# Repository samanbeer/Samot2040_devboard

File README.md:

# SamotPi2040 DevBoard

---

## 📌 Project Overview & Purpose

- **What is it?** A standalone development board based on the Raspberry Pi RP2040 dual-core ARM Cortex-M0+ processor.
- **What does it do?** It provides all essential supporting circuitry (power regulation, Li-Po 3.7V battery charging, automatic power source switching, high-speed crystal oscillator, SPI flash, USB termination, and ESD/pull-down configuration) to run MicroPython, CircuitPython, Arduino, or bare-metal C/C++ Pico SDK code.
- **Why does it exist?** It was created to explore custom PCB design from scratch, master 2-layer routing with fine-pitch QFN and 0402 components, and build a reliable, inexpensive, and customizable devboard for prototyping robotics and embedded electronics.

---

## Why I Made This Project

Because I wanted to design my own RP2040 board with my own design a to be able to say "I made this" with:
1. A modern **USB-C** connector
2. Integrate both **BOOT** and **RESET** switches directly on board to make flashing easy.
3. Provide a full 8MB high-speed SPI Flash storage for large CircuitPython scripts, assets, and datalogging.
4. Integrated **Li-Po 3.7V battery charging** (MCP73831) and **automatic power source switching** (BAT54C Schottky diode) for portable projects.

---

## Project Gallery

### 3D Render

### 3D Board View

### PCB Layout & Routing

### Schematic

---

## Hardware Features & Specifications

| Feature | Specification |
| --- | --- |
| **Microcontroller** | Raspberry Pi RP2040 (Dual-core ARM Cortex-M0+ up to 133 MHz, 264 KB on-chip SRAM) |
| **Flash Memory** | 8 MB (64 Mbit) SPI Flash (Macronix MX25L6433FM2I-08G, SOIC-8) |
| **Power Input** | USB-C 5V VBUS or Li-Po / Li-Ion 3.7V Battery |
| **Battery Charger** | Microchip MCP73831-2-OT (Single-cell Li-Po/Li-Ion linear charge manager, 4.2V CC/CV) |
| **Power Multiplexing** | BAT54C dual Schottky barrier diode (automatic power source switching between USB and Battery) |
| **Voltage Regulation** | Microchip MCP1700T-3302E/TT (3.3V Low-Dropout Regulator, **250mA** output) |
| **Expansion / I/O** | 2x 1x20-pin 2.54mm pitch headers (breadboard compatible) |

---

##  Power Management & Battery Support

The board features a built-in power management circuit designed for both desktop development and portable battery-powered operation:

- **3.7V Li-Po / Li-Ion Battery Support:** Connect any standard 3.7V single-cell Lithium-Polymer (Li-Po) or Lithium-Ion (Li-Ion) battery to the `+BATT` and `GND` pins/pads.
- **Integrated Battery Charging:** The on-board **Microchip MCP73831** charge controller automatically charges the battery when connected to USB-C (5V VBUS) using constant current / constant voltage (CC/CV) up to 4.2V.
- **Automatic Power Source Switching:** A dual common-cathode Schottky diode (**BAT54C**) acts as an automatic power OR-ing switch. When USB-C is plugged in, the board runs directly from USB power while recharging the battery. When USB-C is disconnected, power seamlessly falls over to the battery without interruption or board resets.

---

## 🛠️ Step-by-Step Assembly Guide

> [!IMPORTANT]
> I recommend using HOT airflow station or hot plate for soldering because there are really small components like the main chip or 0402 capacitors/resistors

### Required Tools
- Hot air station / hot plate and soldering iron
- solder flux paste / pen and solder wick
- tweezers
- USB-C data cable

### Assembly Steps

1. **Solder the RP2040 chip:**
   - Apply a thin layer of solder paste to the center thermal pad and other pads.
   - Align first pin of the RP2040 chip using the silkscreen dot marker.
   - Reflow using hot air (~320°C–350°C) or hot plate. Make sure the chip is centered.
2. **Solder the Flash (U3), Voltage Regulator (U2), Charger (U4), and Diode (D1):**
   - Solder the MX25L6433 flash chip (SOIC-8), MCP1700 (SOT-23), MCP73831 charger (SOT-23-5), and BAT54C diode (SOT-23). You can do this with normal soldering iron and plenty of flux.
3. **Solder Passives (Resistors & Capacitors) and Crystal:**
   - Solder the small 0402 capacitors (C1–C12, C17, C18) close to the RP2040 power pins.
   - Solder the 0603 capacitors (C13, C14), crystal load capacitors (C15, C16), and resistors (R1–R7, R9).
   - Then carefully solder the 12 MHz crystal (Y1).
4. **Solder USB-C (J1):**
   - Align the 16-pin USB-C receptacle (GCT USB4085). Solder the through-hole shielding legs for mechanical strength, then use a iron tip with a lot of flux to solder the other pins.
5. **Solder buttons(SW1, SW2):**
   - Solder the swithces for BOOT and RESET.
6. **Double check :**
   - Inspect all solder joidnts under magnification for solder bridges or cold joints (especially on the RP2040 and USB-C).
   - Using a multimeter in continuity/resistance mode, verify that `VBUS` (5V), `3V3`, and `GND` are **not shorted**.
7. **Solder Pin Headers (J2, J3, ):**
   - Insert the 1x20 2.54mm male headers into a solderless breadboard to keep them perpendicular, place the PCB on top, and solder each pin.

---

##  How to Flash Firmware

The RP2040 has a built-in ROM bootloader that makes flashing firmware simple without requiring external programmers:

```mermaid
flowchart LR
    A["Hold BOOT"] --> B["Plug in USB-C"]
    B --> C["'RPI-RP2' Drive Appears"]
    C --> D["Drag & Drop .UF2 File"]
    D --> E["Auto Reboot & Run!"]
```

1. **Enter Bootloader Mode:**
   - Hold the **`BOOT`** button (SW1).
   - Connect the board to computer using a USB-C data cable 
   - Release the `BOOT` button.
3. **Flashing Firmware:**
   - Drag and drop your compiled **`.uf2`** firmware file onto the `RPI-RP2` drive that should appear on PC:
     - **MicroPython:** Download the [Official RP2040 MicroPython UF2](https://micropython.org/download/rp2-pico/).
     - **CircuitPython:** Download the [Adafruit CircuitPython RP2040 UF2](https://circuitpython.org/board/raspberry_pi_pico/).
     - **C/C++ SDK / Arduino:** Build your project using Arduino IDE (with Earle Philhower RP2040 core) or Pico SDK and drag the resulting `.uf2` file.
4. **Execution:**
   - Once the `.uf2` file finishes copying, the board will automatically dismount and execute the program immediately.

---

## BOM

> Import [`quickOrder_TME.csv`](quickOrder_TME.csv) directly to [TME.eu](https://tme.eu) for fast order.

| Qty | Value | Reference | Footprint | Where | Cost (USD) |
|:---:|:---|:---|:---|:---|:---:|
| 1 | **RP2040** | U1 | QFN-56-1EP (7x7mm, 0.4mm pitch) | [TME LINK](https://www.tme.eu/cz/details/sc0914-7/raspberry-pi-vestavene-systemy/raspberry-pi/ic-rp2040-rp2b2-t-r-500-7-reel/) | $1.02 |
| 1 | **MX25L6433FM2I-08G** (8MB Flash) | U3 | SOIC-8 (5.3x5.3mm, 1.27mm pitch) | [TME LINK](https://www.tme.eu/cz/details/mx25l6433fm2i-08g/pameti-flash-seriove/macronix-international/mx25l6433fm2i-08g-tube/) | $2.40 |
| 1 | **MCP1700T-3302E/TT** (3.3V LDO) | U2 | SOT-23 | [TME LINK](https://www.tme.eu/cz/details/mcp1700t-3302e_tt/stabilizatory-napeti-neregulovane-ldo/microchip-technology/) | $0.65 |
| 1 | **12 MHz Crystal** | Y1 | SMD 3225-4Pin (3.2x2.5mm) | [TME LINK](https://www.tme.eu/cz/details/abm8g-12.000mhz-18/resonators-and-generators/abracon/abm8g-12-000mhz-18-d2y-t/) | $0.39 |
| 1 | **USB-C Receptacle 16P** | J1 | GCT_USB4105 | [TME LINK](https://www.tme.eu/cz/details/usb4105-gf-a/konektory-usb-a-ieee1394/gct/) | $0.75 |
| 2 | **Tactile Switch SPST** | SW1, SW2 | SMD (Omron B3U-1000P-B) | [TME LINK](https://www.tme.eu/cz/details/b3u-1000pb/mikrospinace-tact/omron-electronic-components/b3u-1000p-b/) | $1.95 |
| 12 | **0.1 µF (100nF) 16V** | C2, C3, C4, C5, C6, C7, C8, C9, C11, C12, C17, C18 | C_0402 (1005 Metric) | [TME LINK](https://www.tme.eu/cz/details/grm155r71c104ka88d/kondenzatory-mlcc-smd/murata/) | $0.17 |
| 2 | **1 µF 25V** | C1, C10 | C_0402 (1005 Metric) | [TME LINK](https://www.tme.eu/cz/details/grm155r61e105ma12d/kondenzatory-mlcc-smd/murata/) | $0.095 |
| 4 | **10 µF 10V** | C13, C14, C19, C20 | C_0603 (1608 Metric) | [TME LINK](https://www.tme.eu/cz/details/lmk107bj106maltd/kondenzatory-mlcc-smd/taiyo-yuden/lmk107-bj106maltd/) | $0.60 |
| 2 | **27 pF 50V** | C15, C16 | C_0603 (1608 Metric) | [TME LINK](https://www.tme.eu/cz/details/cc0603jrnpo9270/kondenzatory-mlcc-smd/yageo/cc0603jrnpo9bn270/) | $0.043 |
| 2 | **27 Ω 1%** | R3, R4 | R_0402 (1005 Metric) | [TME LINK](https://www.tme.eu/cz/details/erj2rkf27r0x/rezistory-smd/panasonic/) | $0.25 |
| 2 | **5.1 kΩ 1%** | R1, R2 | R_0603 (1608 Metric) | [TME LINK](https://www.tme.eu/cz/details/wr06x5101ftl/rezistory-smd/walsin/) | $0.18 |
| 2 | **1 kΩ 1%** | R5, R6 | R_0603 (1608 Metric) | [TME LINK](https://www.tme.eu/cz/details/crcw06031k00fkea/rezistory-smd/vishay/) | $0.015 |
| 2 | **10 kΩ 1%** | R7, R8, R9 | R_0603 (1608 Metric) | [TME LINK](https://www.tme.eu/cz/details/rc0603jr-0710k/rezistory-smd/yageo/rc0603jr-0710kl/) | $0.15 |
| 2 | **Pin Header 1x20 (2.54mm)** | J2, J3 | PinHeader_1x20_P2.54mm_Vertical | [TME LINK](https://www.tme.eu/cz/details/sl8.20z/konektory-hrebinky/fischer-elektronik/10057879/) | $4.5(I dont need these. Already own) |
| 1 | **MCP73831-2-OT** | U4 | SOT-23-5_HandSoldering | [TME LINK](https://www.tme.eu/cz/details/mcp73831t-2aci_ot/kontrolery-baterii-a-akumulat-obvody/microchip-technology/) | ~$0.75 |
| 1 | **BAT54C** | D1 | SOT-23_Handsoldering | [TME LINK](https://www.tme.eu/cz/details/bat54c-aks/diody-schottky-smd/akyga-semi/aks0016/) | ~$0.07 |
| 1 | **Li-Po 3.7V Battery** | - | - | [TME LINK](https://www.tme.eu/cz/details/aky-lp401235/akumulatory/akyga-battery/aky0475/) | ~$5.7 |
| 1 | **PCB ** | PCB | 2-layer FR-4 (1.6mm, ENIG/HASL) | [JLCPCB](https://jlcpcb.com) | ~$13.45 |
| - | **Estimated Shipping** | - | - | - | ~$8.21 |
| **Total** | | | | | **~$41,34** |

### JLCPCB Cart:

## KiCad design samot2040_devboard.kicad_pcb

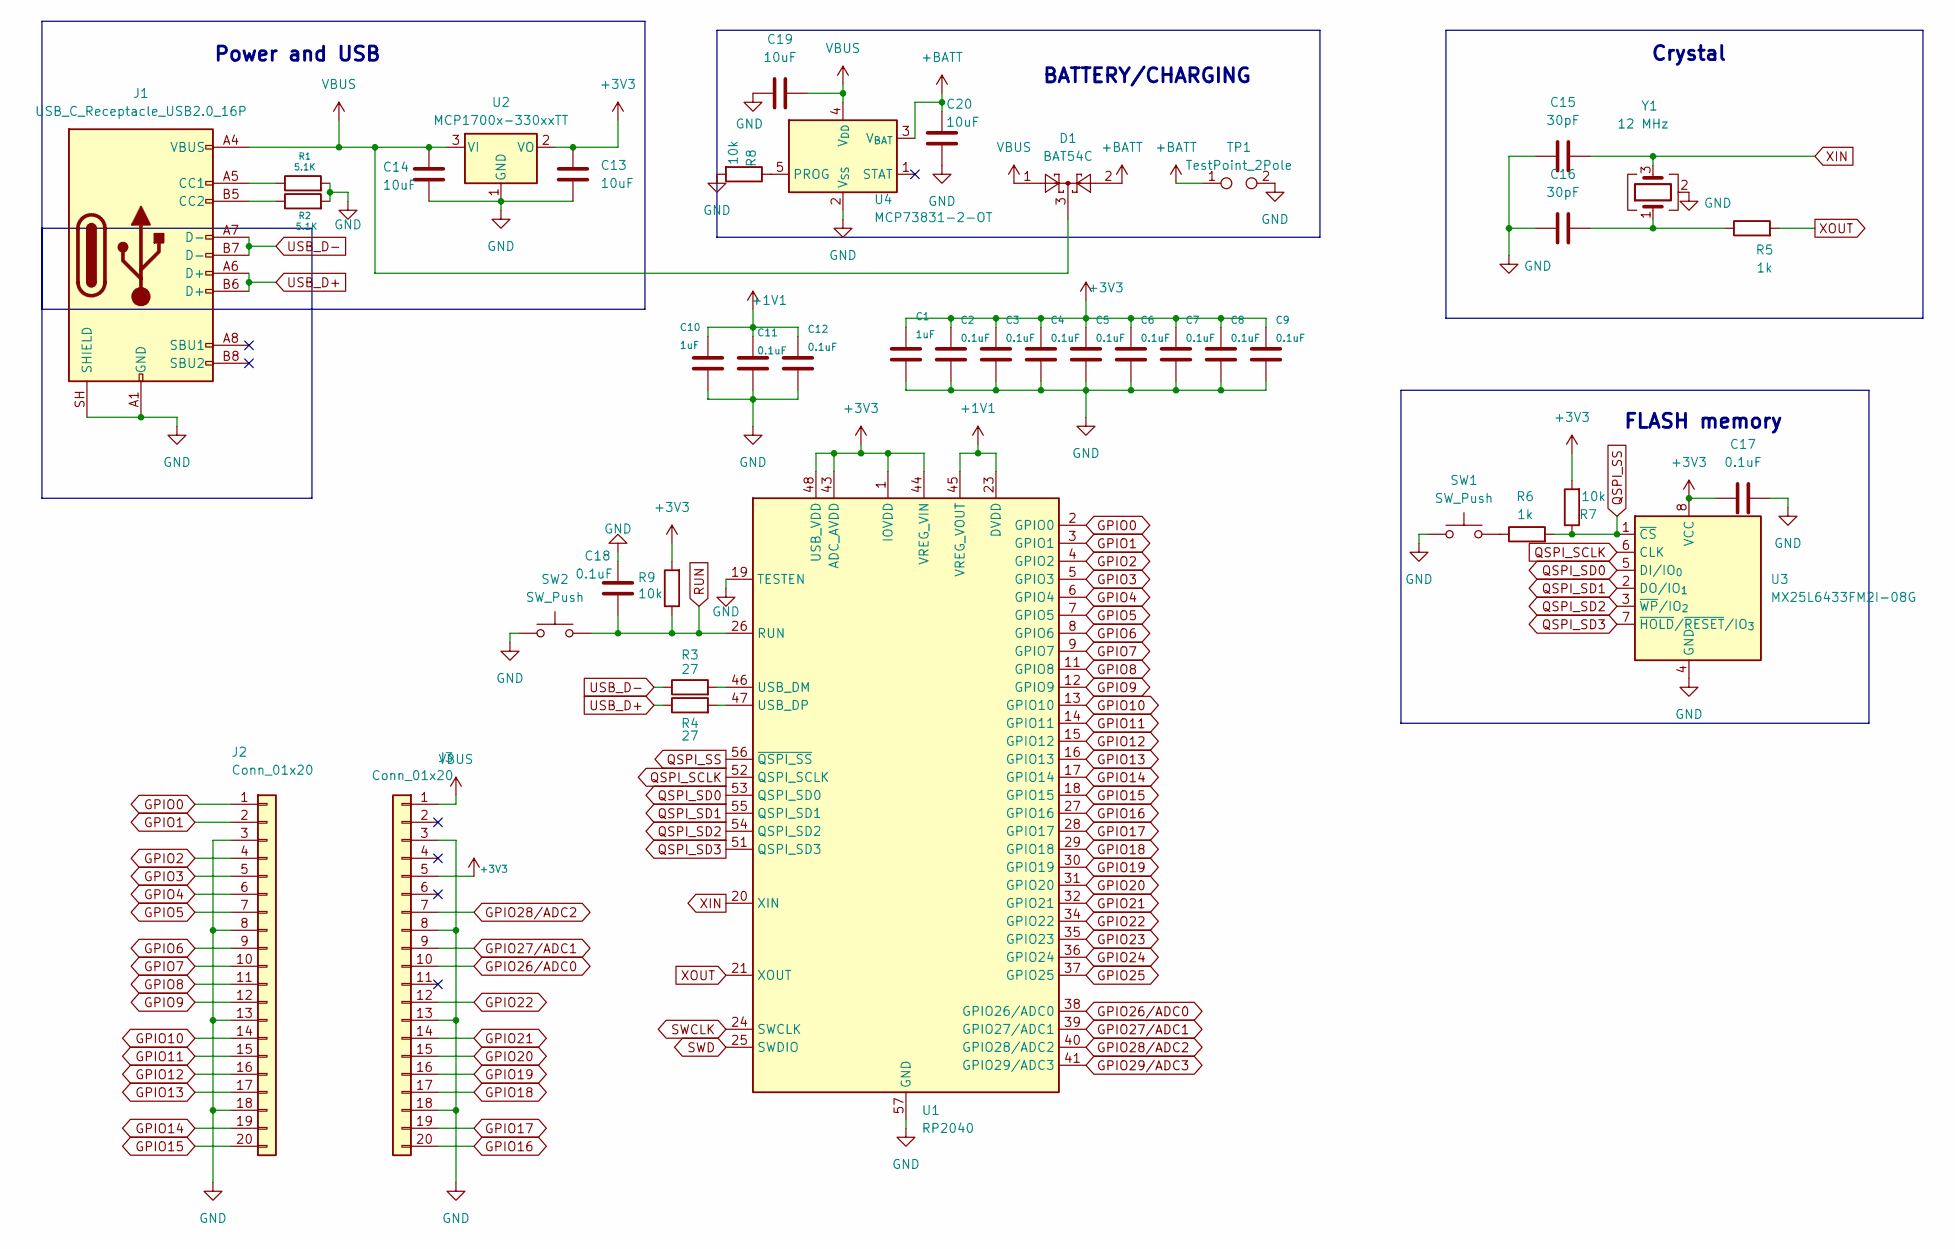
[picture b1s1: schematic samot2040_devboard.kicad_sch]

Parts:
C1, C10: 1uF; C_0402_1005Metric_Pad0.74x0.62mm_HandSolder
C2, C3, C4, C5, C6, C7, C8, C9, C11, C12, C17, C18: 0.1uF; C_0402_1005Metric_Pad0.74x0.62mm_HandSolder
C13, C14, C19, C20: 10uF; C_0603_1608Metric_Pad1.08x0.95mm_HandSolder
C15, C16: 30pF; C_0603_1608Metric_Pad1.08x0.95mm_HandSolder
D1: BAT54C; SOT-23_Handsoldering
J1: USB_C_Receptacle_USB2.0_16P; USB_C_Receptacle_GCT_USB4105-xx-A_16P_TopMnt_Horizontal
J2, J3: Conn_01x20; PinHeader_1x20_P2.54mm_Vertical
R1, R2: 5.1K; R_0603_1608Metric_Pad0.98x0.95mm_HandSolder
R3, R4: 27; R_0402_1005Metric_Pad0.72x0.64mm_HandSolder
R5, R6: 1k; R_0603_1608Metric_Pad0.98x0.95mm_HandSolder
R7, R8, R9: 10k; R_0603_1608Metric_Pad0.98x0.95mm_HandSolder
SW1, SW2: SW_Push; SW_SPST_B3U-1000P-B
TP1: TestPoint_2Pole; TestPoint_2Pads_Pitch2.54mm_Drill0.8mm
U1: RP2040; QFN-56-1EP_7x7mm_P0.4mm_EP3.2x3.2mm
U2: MCP1700x-330xxTT; SOT-23
U3: MX25L6433FM2I-08G; SOIC-8_5.3x5.3mm_P1.27mm
U4: MCP73831-2-OT; SOT-23-5_HandSoldering
Y1: 12 MHz; Crystal_SMD_3225-4Pin_3.2x2.5mm_HandSoldering

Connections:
+1V1: C10.1, C11.1, C12.1, U1.23 (DVDD), U1.45 (VREG_VOUT), U1.50 (DVDD)
+3V3: C1.1, C2.1, C3.1, C4.1, C5.1, C6.1, C7.1, C8.1, C9.1, C13.1, C17.1, J3.5, R7.2, R9.2, U1.1 (IOVDD), U1.10 (IOVDD), U1.22 (IOVDD), U1.33 (IOVDD), U1.42 (IOVDD), U1.43 (ADC_AVDD), U1.44 (VREG_VIN), U1.48 (USB_VDD), U1.49 (IOVDD), U2.2 (VO), U3.8 (VCC)
+BATT: C20.2, D1.2, TP1.1, U4.3 (V_{BAT})
GND: C1.2, C2.2, C3.2, C4.2, C5.2, C6.2, C7.2, C8.2, C9.2, C10.2, C11.2, C12.2, C13.2, C14.2, C15.1, C16.1, C17.2, C18.1, C19.1, C20.1, J1.A1 (GND), J1.A12 (GND), J1.B1 (GND), J1.B12 (GND), J1.SH (SHIELD), J2.3, J2.8, J2.13, J2.18, J3.3, J3.8, J3.13, J3.18, R1.2, R2.2, R8.2, SW1.1, SW2.1, TP1.2, U1.19 (TESTEN), U1.57 (GND), U2.1 (GND), U3.4 (GND), U4.2 (V_{SS}), Y1.2 (G), Y1.4 (G)
GPIO0: J2.1, U1.2 (GPIO0)
GPIO1: J2.2, U1.3 (GPIO1)
GPIO2: J2.4, U1.4 (GPIO2)
GPIO3: J2.5, U1.5 (GPIO3)
GPIO4: J2.6, U1.6 (GPIO4)
GPIO5: J2.7, U1.7 (GPIO5)
GPIO6: J2.9, U1.8 (GPIO6)
GPIO7: J2.10, U1.9 (GPIO7)
GPIO8: J2.11, U1.11 (GPIO8)
GPIO9: J2.12, U1.12 (GPIO9)
GPIO10: J2.14, U1.13 (GPIO10)
GPIO11: J2.15, U1.14 (GPIO11)
GPIO12: J2.16, U1.15 (GPIO12)
GPIO13: J2.17, U1.16 (GPIO13)
GPIO14: J2.19, U1.17 (GPIO14)
GPIO15: J2.20, U1.18 (GPIO15)
GPIO16: J3.20, U1.27 (GPIO16)
GPIO17: J3.19, U1.28 (GPIO17)
GPIO18: J3.17, U1.29 (GPIO18)
GPIO19: J3.16, U1.30 (GPIO19)
GPIO20: J3.15, U1.31 (GPIO20)
GPIO21: J3.14, U1.32 (GPIO21)
GPIO22: J3.12, U1.34 (GPIO22)
GPIO23: U1.35 (GPIO23)
GPIO24: U1.36 (GPIO24)
GPIO25: U1.37 (GPIO25)
GPIO26/ADC0: J3.10, U1.38 (GPIO26/ADC0)
GPIO27/ADC1: J3.9, U1.39 (GPIO27/ADC1)
GPIO28/ADC2: J3.7, U1.40 (GPIO28/ADC2)
GPIO29/ADC3: U1.41 (GPIO29/ADC3)
unnamed: C16.2, R5.1, Y1.1
unnamed: J1.A5 (CC1), R1.1
unnamed: J1.B5 (CC2), R2.1
unnamed: R6.1, SW1.2
unnamed: R3.2, U1.46 (USB_DM)
unnamed: R4.2, U1.47 (USB_DP)
unnamed: R8.1, U4.5 (PROG)
QSPI_SCLK: U1.52 (QSPI_SCLK), U3.6 (CLK)
QSPI_SD0: U1.53 (QSPI_SD0), U3.5 (DI/IO_{0})
QSPI_SD1: U1.55 (QSPI_SD1), U3.2 (DO/IO_{1})
QSPI_SD2: U1.54 (QSPI_SD2), U3.3 (~WP/IO_{2})
QSPI_SD3: U1.51 (QSPI_SD3), U3.7 (~HOLD/~RESET/IO_{3})
QSPI_SS: R6.2, R7.1, U1.56 (~QSPI_SS), U3.1 (~CS)
RUN: C18.2, R9.1, SW2.2, U1.26 (RUN)
SWCLK: U1.24 (SWCLK)
SWD: U1.25 (SWDIO)
USB_D+: J1.A6 (D+), J1.B6 (D+), R4.1
USB_D-: J1.A7 (D-), J1.B7 (D-), R3.1
VBUS: C14.1, C19.2, D1.1, D1.3, J1.A4 (VBUS), J1.A9 (VBUS), J1.B4 (VBUS), J1.B9 (VBUS), J3.1, U2.3 (VI), U4.4 (V_{DD})
XIN: C15.2, U1.20 (XIN), Y1.3
XOUT: R5.2, U1.21 (XOUT)

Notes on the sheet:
Power and USB
Crystal
BATTERY/CHARGING
FLASH memory

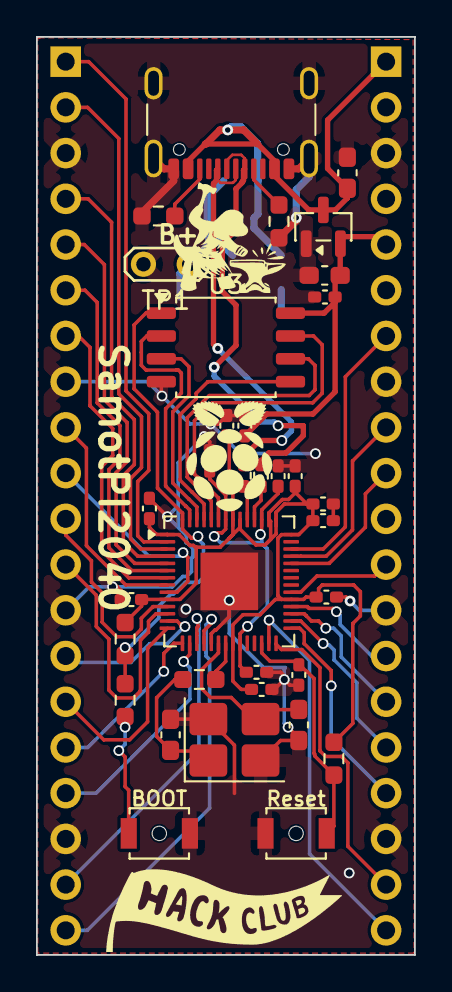
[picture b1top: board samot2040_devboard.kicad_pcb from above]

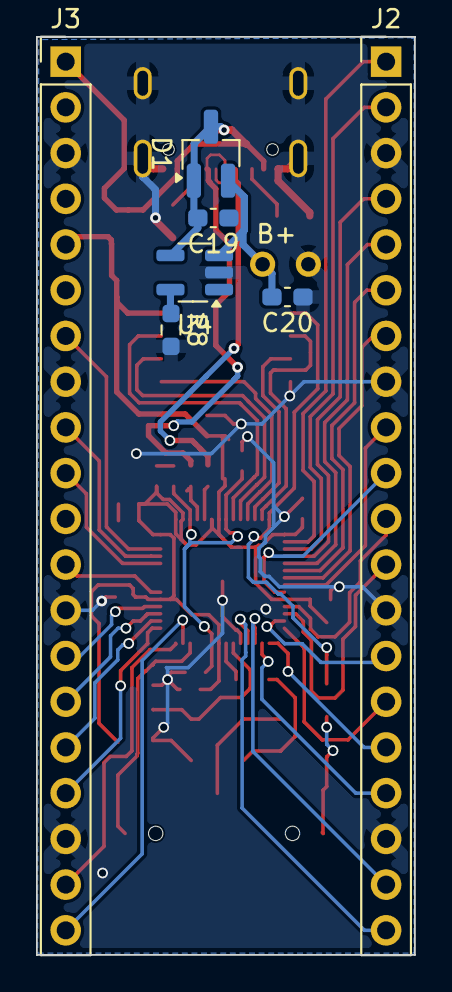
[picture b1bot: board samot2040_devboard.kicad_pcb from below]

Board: 2 copper layers, 21.0 x 51.0 mm, 41 parts (7 on the bottom side), 49 nets.

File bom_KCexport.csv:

"Reference","Qty","Value","Footprint"
"C1,C10","2","1uF","Capacitor_SMD:C_0603_1608Metric_Pad1.08x0.95mm_HandSolder"
"C2,C3,C4,C5,C6,C7,C8,C9,C11,C12,C17,C18","12","0.1uF","Capacitor_SMD:C_0603_1608Metric_Pad1.08x0.95mm_HandSolder"
"C13,C14","2","10uF","Capacitor_SMD:C_0603_1608Metric_Pad1.08x0.95mm_HandSolder"
"C15,C16","2","30pF","Capacitor_SMD:C_0603_1608Metric_Pad1.08x0.95mm_HandSolder"
"J1","1","USB_C_Receptacle_USB2.0_16P","Connector_USB:USB_C_Receptacle_GCT_USB4085"
"J2,J3","2","Conn_01x20","Connector_PinHeader_2.54mm:PinHeader_1x20_P2.54mm_Vertical"
"J4","1","Conn_01x03","Connector_PinHeader_2.54mm:PinHeader_1x03_P2.54mm_Vertical"
"R1,R2","2","5.1K","Resistor_SMD:R_0603_1608Metric_Pad0.98x0.95mm_HandSolder"
"R3,R4","2","27","Resistor_SMD:R_0603_1608Metric_Pad0.98x0.95mm_HandSolder"
"R5,R6","2","1k","Resistor_SMD:R_0603_1608Metric_Pad0.98x0.95mm_HandSolder"
"R7,R9","2","10k","Resistor_SMD:R_0603_1608Metric_Pad0.98x0.95mm_HandSolder"
"SW1,SW2","2","SW_Push","Button_Switch_SMD:SW_SPST_B3U-1000P-B"
"U1","1","RP2040","Package_DFN_QFN:QFN-56-1EP_7x7mm_P0.4mm_EP3.2x3.2mm"
"U2","1","MCP1700x-330xxTT","Package_TO_SOT_SMD:SOT-23"
"U3","1","MX25L6433FM2I-08G","Package_SO:SOIC-8_5.3x5.3mm_P1.27mm"
"Y1","1","12 MHz","Crystal:Crystal_SMD_3225-4Pin_3.2x2.5mm_HandSoldering"
